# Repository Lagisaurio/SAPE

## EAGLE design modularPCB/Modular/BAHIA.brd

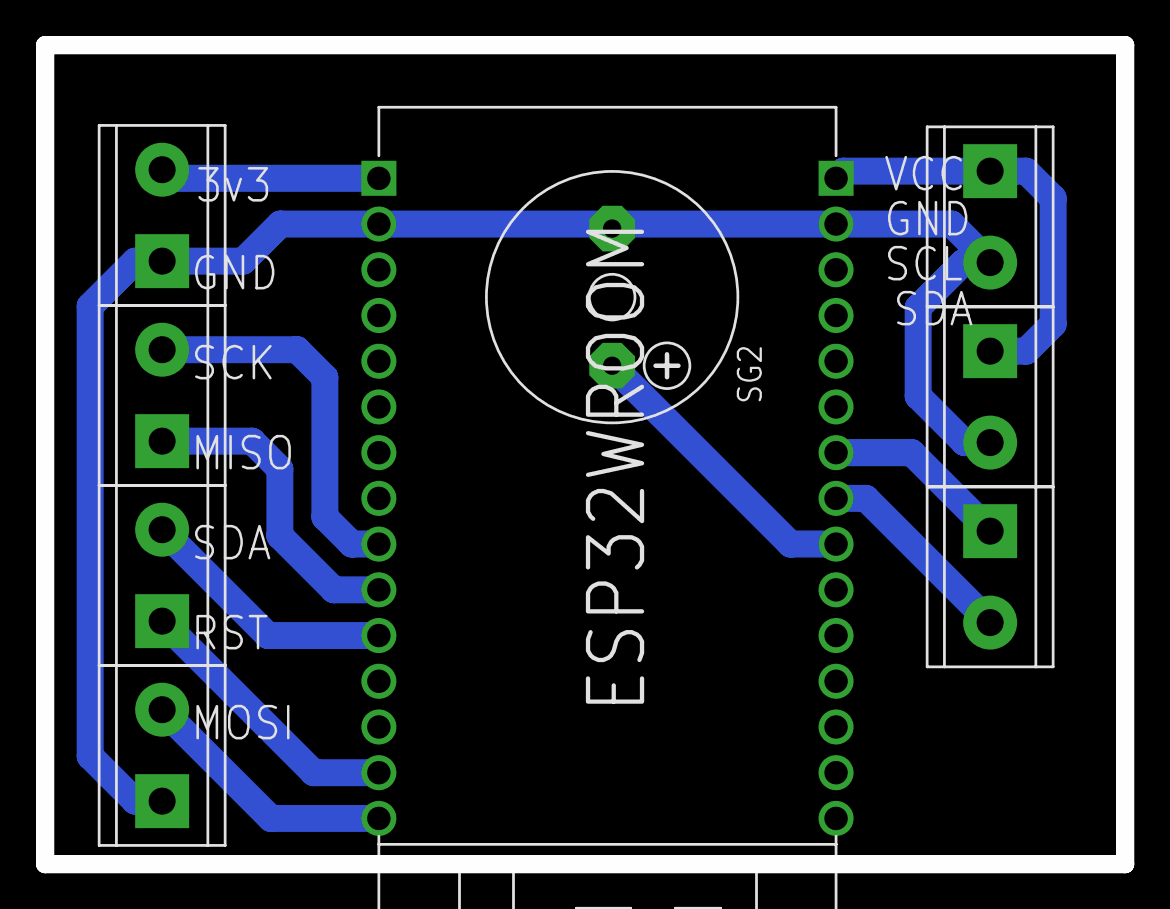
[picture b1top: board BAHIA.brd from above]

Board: 2 copper layers, 60.0 x 45.5 mm, 9 parts (0 on the bottom side), 11 nets.

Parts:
SG2: F/CM12P
U$1: ESP32WROOM
U$2, U$3, U$4, U$5, U$6, U$7, U$8: CLEMAS

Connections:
3V3: U$1.3V3, U$5.2
BUZZER: SG2.+, U$1.D33
GND: SG2.-, U$1.GND@0, U$1.GND@1, U$2.1, U$5.1, U$6.2, U$7.2
MISO: U$1.D19, U$4.1
MOSI: U$1.D23, U$2.2
RST: U$1.D22, U$3.1
SCK: U$1.D18, U$4.2
SCL: U$1.D26, U$8.1
SDA: U$1.D21, U$3.2
SDA_I2C: U$1.D25, U$8.2
VCC: U$1.VIN, U$6.1, U$7.1

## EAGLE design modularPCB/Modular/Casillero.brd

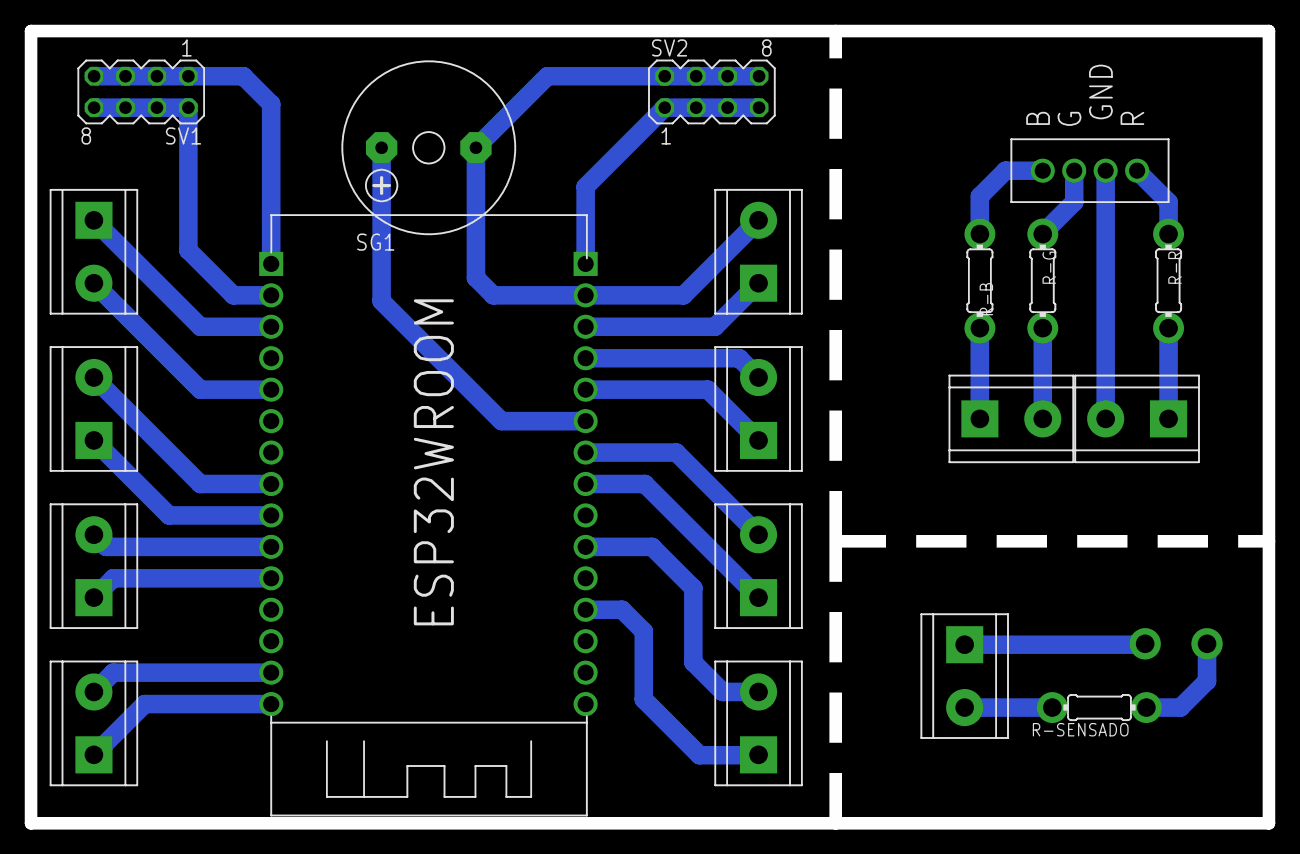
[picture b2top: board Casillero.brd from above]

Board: 2 copper layers, 100.0 x 64.0 mm, 20 parts (0 on the bottom side), 22 nets.

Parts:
R-B: 220; 0204/7
R-G: 220; 0204/7
R-R: 220; 0204/7
R-SENSADO: 220; 0204/7
SG1: F/CM12P
SV1, SV2: MA04-2
U$1: ESP32WROOM
U$2, U$4, U$5, U$6, U$7, U$8, U$9, U$10, U$11, U$12, U$13: CLEMAS
U$3: LEDRGB

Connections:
3V3: SV1.1, SV1.3, SV1.5, SV1.7, U$1.3V3
BUZZER: SG1.+, U$1.D27
CERRADURA_CTRL: U$1.D25, U$8.1
CERRADURA_VCC: U$1.D26, U$8.2
GA_DT: U$1.D19, U$4.2
GA_LED: U$1.D21, U$4.1
GA_SCK: U$1.D18, U$5.1
GND: SG1.-, SV1.2, SV1.4, SV1.6, SV1.8, SV2.2, SV2.4, SV2.6, SV2.8, U$1.GND@0, U$1.GND@1, U$3.GND, U$10.2, U$12.2, U$13.1
IR: U$1.D34, U$7.1
LCD_SCL: U$1.D5, U$5.2
LCD_SDA: U$1.D15, U$6.1
LED_B: R-B.2, U$1.D14, U$9.1, U$11.1
LED_G: R-G.2, U$1.D12, U$9.2, U$11.2
LED_R: R-R.2, U$1.D13, U$10.1, U$12.1
unnamed: R-R.1, U$3.R
unnamed: R-G.1, U$3.G
unnamed: R-B.1, U$3.B
SENSADO_LED: R-SENSADO.2, U$1.D4, U$6.2, U$13.2
UL_ECHO: U$1.D22, U$2.2
UL_LED: U$1.D32, U$7.2
UL_TRG: U$1.D23, U$2.1
VIN: SV2.1, SV2.3, SV2.5, SV2.7, U$1.VIN

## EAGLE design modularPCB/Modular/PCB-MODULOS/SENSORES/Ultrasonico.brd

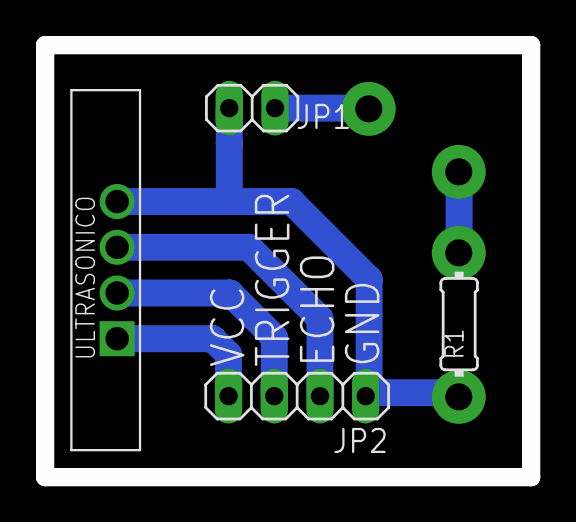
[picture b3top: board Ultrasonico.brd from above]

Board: 2 copper layers, 27.0 x 24.0 mm, 4 parts (0 on the bottom side), 5 nets.

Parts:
JP1: 1X02
JP2: 1X04
R1: 220; 0204/7
U$1: ULTRASONICO

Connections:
ECHO: JP2.2, U$1.ECHO
GND: JP1.2, JP2.1, R1.1, U$1.GND
PULSO-ULTRASONICO: JP1.1, R1.2
TRIGGER: JP2.3, U$1.TRIG
VCC: JP2.4, U$1.VCC

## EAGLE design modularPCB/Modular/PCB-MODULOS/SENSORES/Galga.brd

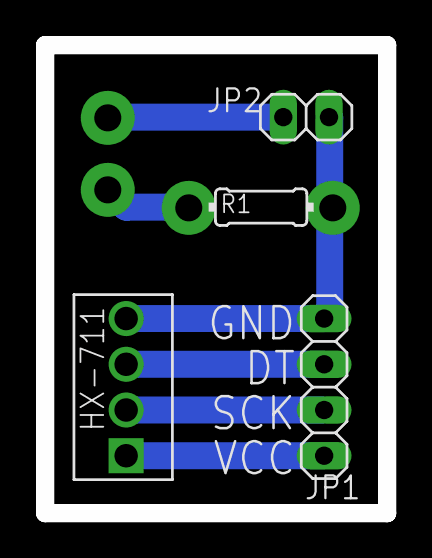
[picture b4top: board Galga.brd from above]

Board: 2 copper layers, 19.0 x 26.0 mm, 4 parts (0 on the bottom side), 4 nets.

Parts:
JP1: 1X04
JP2: 1X02
R1: 220; 0204/7
U$2: HX-711

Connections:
3V3: JP1.4, U$2.VCC
DT-GALGA: JP1.2, U$2.DT
GND: JP1.1, JP2.2, R1.1, U$2.GND
SCK-GALGA: JP1.3, U$2.SCK

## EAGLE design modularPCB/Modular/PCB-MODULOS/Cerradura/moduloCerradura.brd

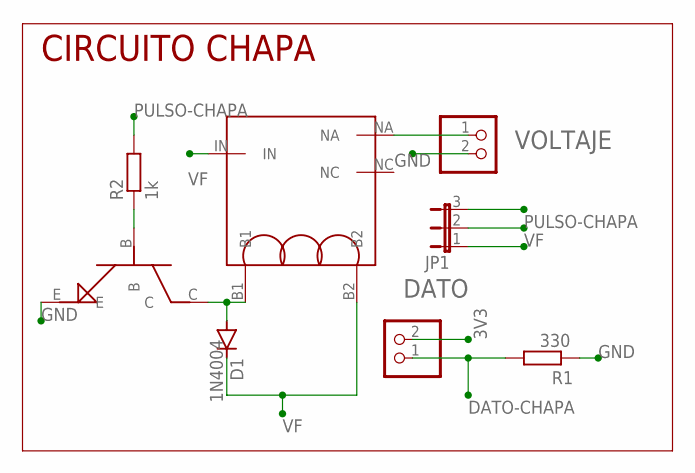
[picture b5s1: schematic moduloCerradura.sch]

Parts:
D1: 1N4004; DO41-10
DATO: PINHD-1X2; 1X02
JP1: JP2E; JP2
R1: 330; 0204/7
R2: 1k; 0204/7
U$1: 2N2222
U$2: RELEY
VOLTAJE: PINHD-1X2; 1X02

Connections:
3V3: DATO.2
DATO-CHAPA: DATO.1, R1.2
GND: JP1.3, R1.1, U$1.E, VOLTAJE.2
unnamed: R2.1, U$1.B
unnamed: D1.A, U$1.C, U$2.B1
unnamed: U$2.NA, VOLTAJE.1
PULSO-CHAPA: JP1.2, R2.2
VF: D1.C, JP1.1, U$2.B2, U$2.IN

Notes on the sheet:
CIRCUITO CHAPA

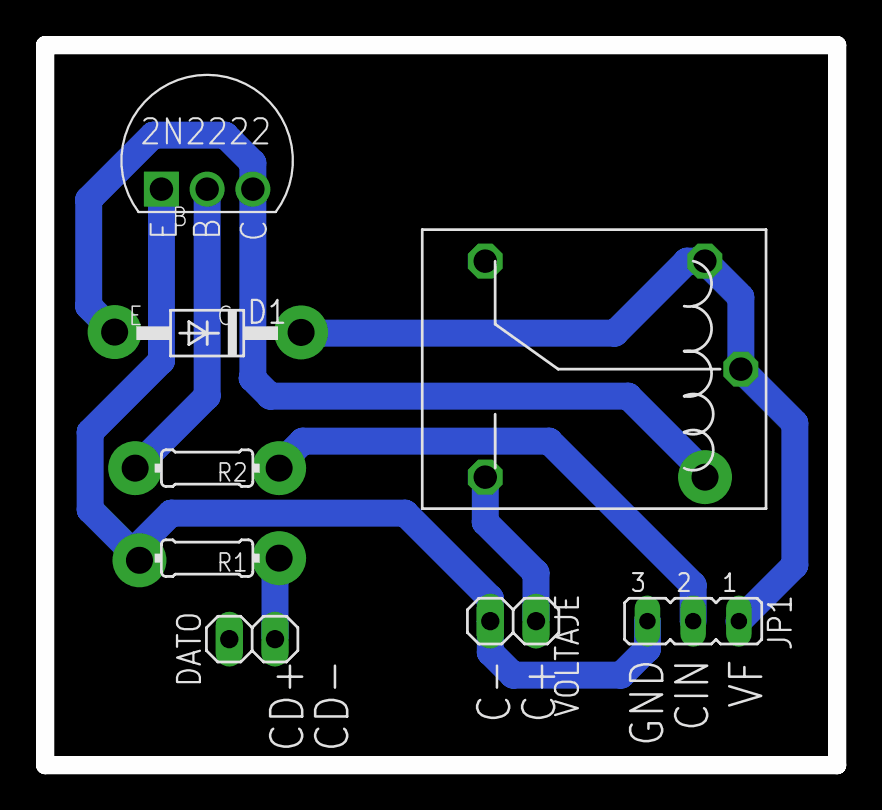
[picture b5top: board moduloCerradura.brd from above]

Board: 2 copper layers, 44.0 x 40.0 mm, 8 parts (0 on the bottom side), 7 nets.

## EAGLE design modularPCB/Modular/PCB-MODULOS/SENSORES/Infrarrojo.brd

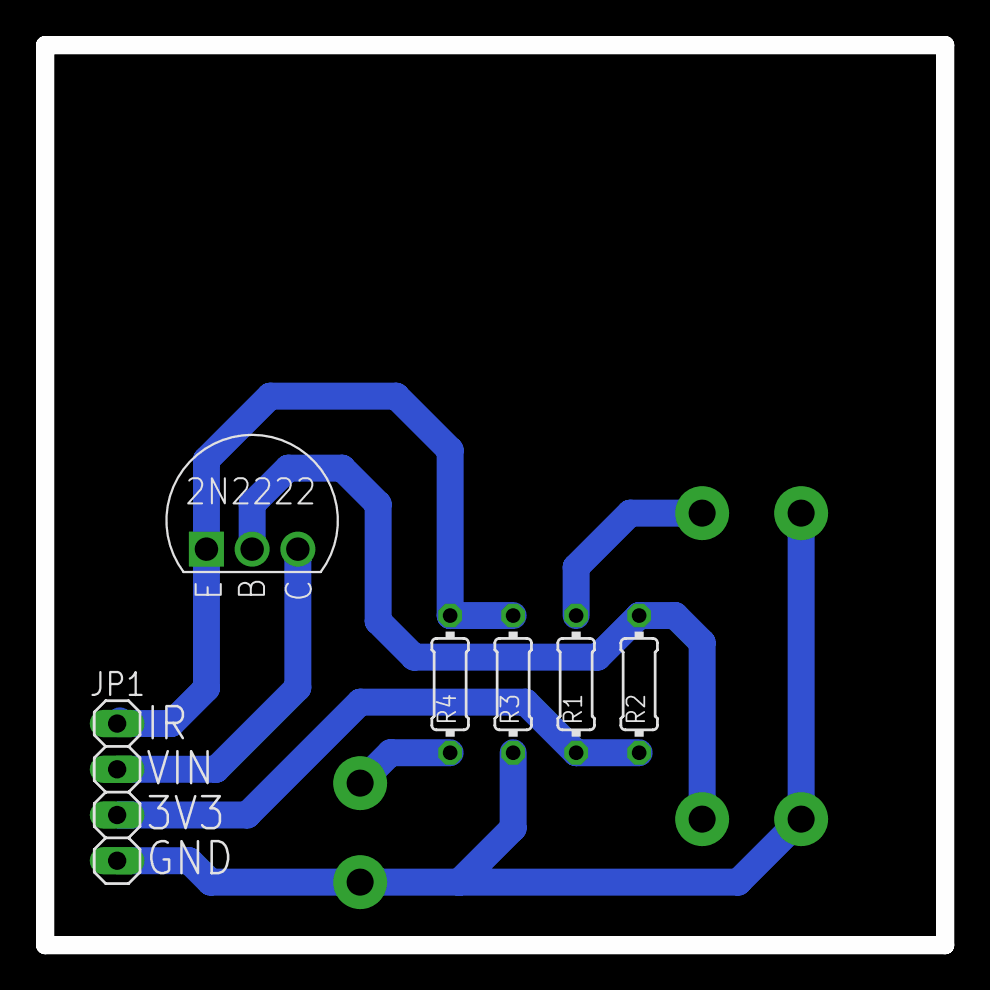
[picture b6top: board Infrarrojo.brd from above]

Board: 2 copper layers, 50.0 x 50.0 mm, 6 parts (0 on the bottom side), 5 nets.

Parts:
JP1: 1X04
R1: 380; 0204/7
R2, R3: 22K; 0204/7
R4: 220; 0204/7
U$1: 2N2222

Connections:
3V3: JP1.2, R1.2, R2.2
GND: JP1.1, R3.2
PULSO-INFRA: JP1.4, R3.1, R4.2, U$1.E
RECEPTOR: R2.1, U$1.B
VIN: JP1.3, U$1.C

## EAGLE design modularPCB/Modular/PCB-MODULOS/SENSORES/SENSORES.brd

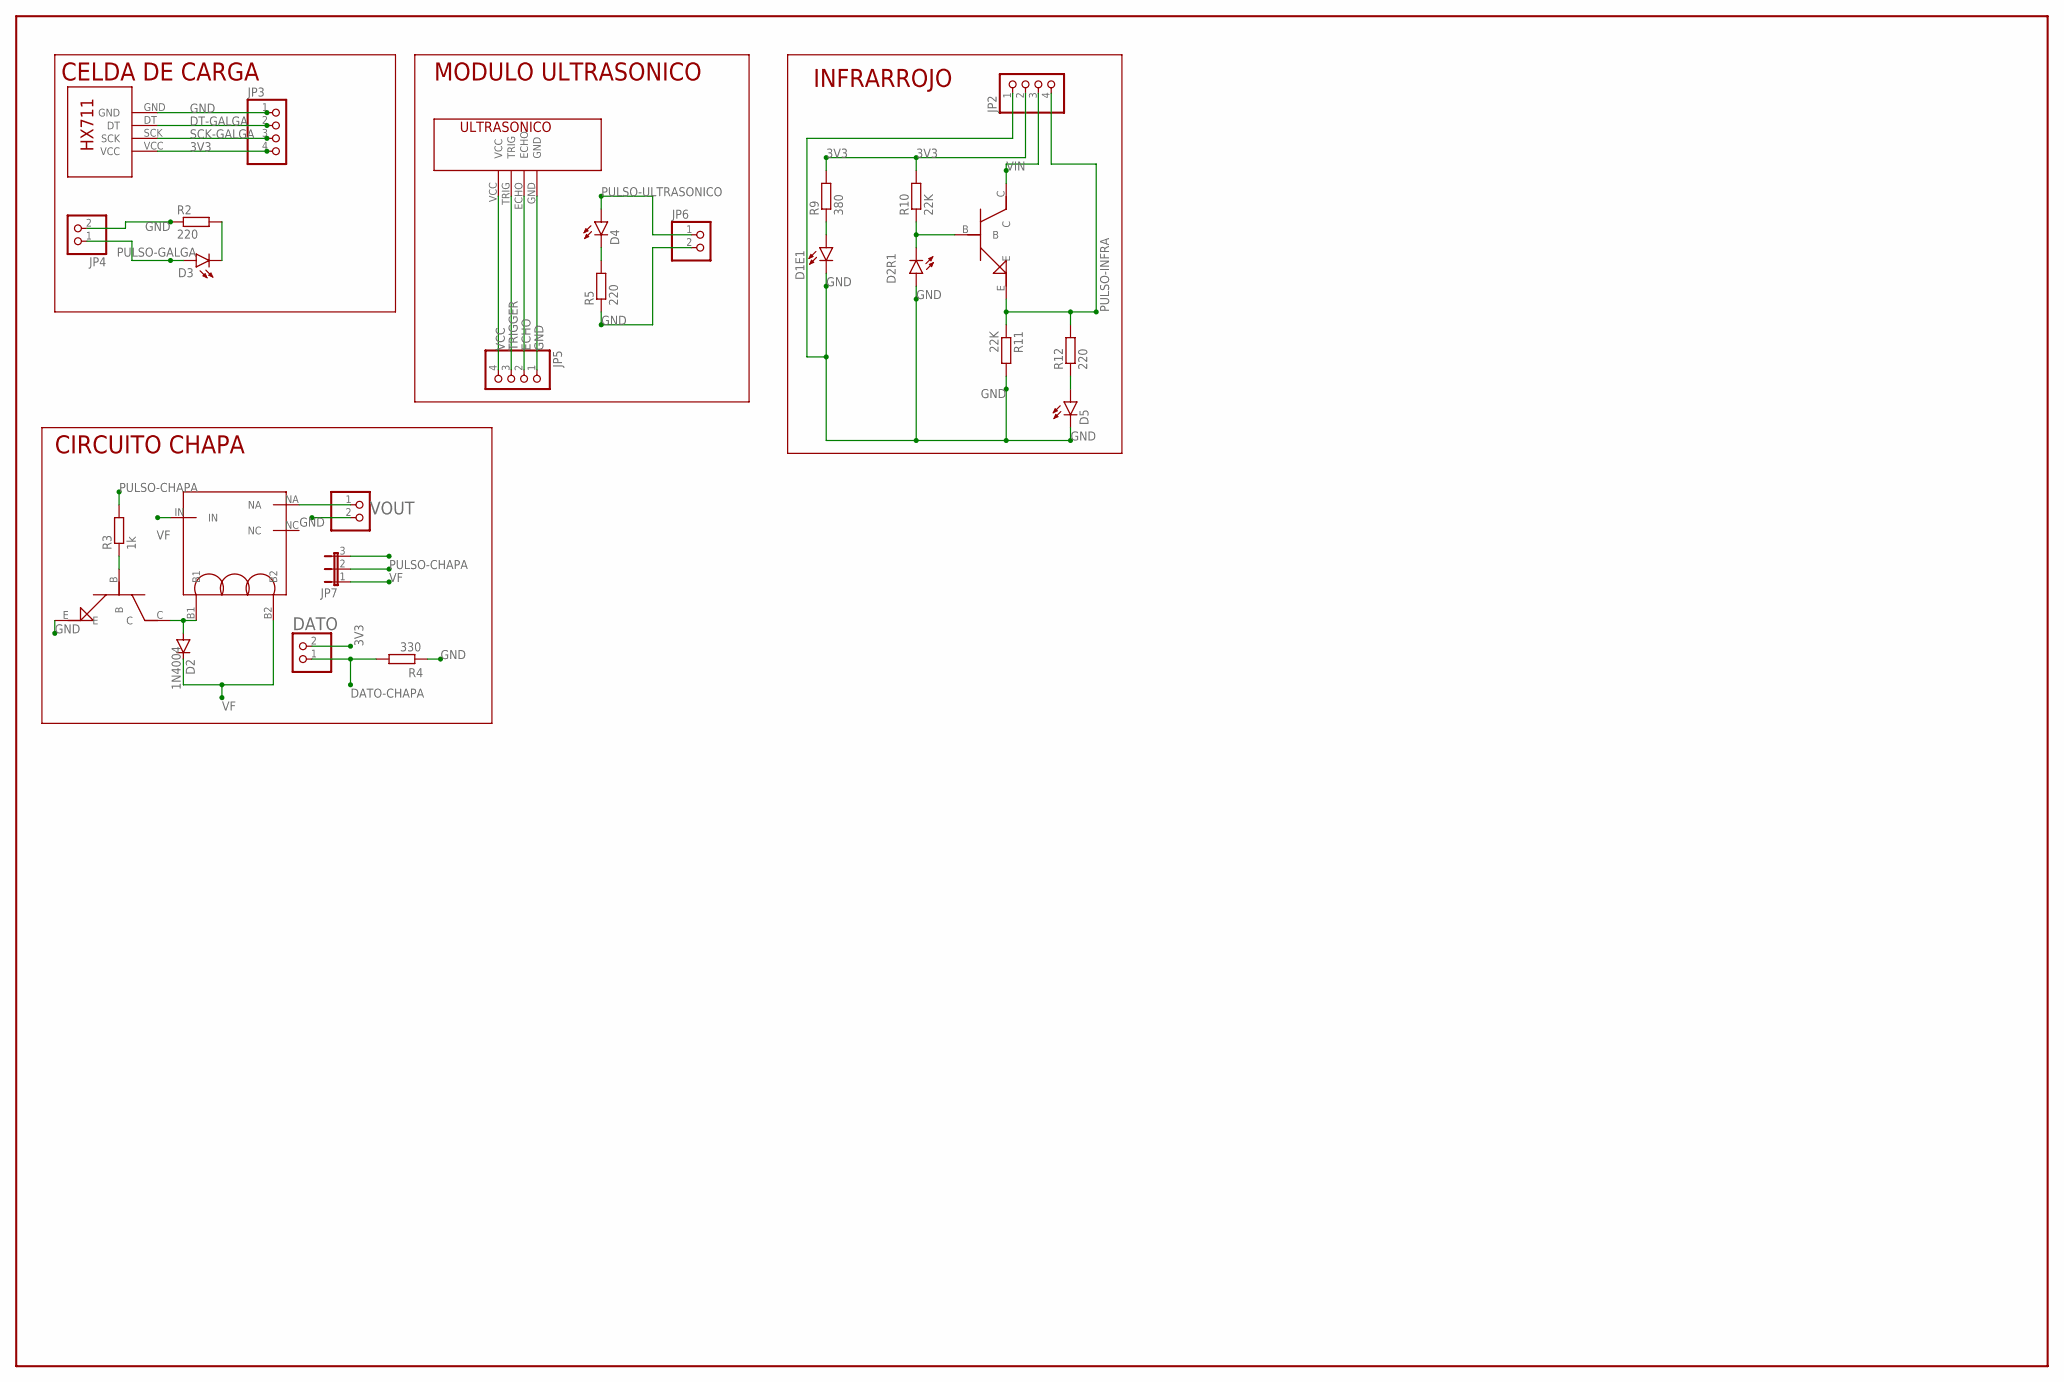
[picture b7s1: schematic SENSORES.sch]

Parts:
D1E1, D2R1, D3, D4, D5: LED3MM
D2: 1N4004; DO41-10
DATO: PINHD-1X2; 1X02
JP2, JP3, JP5: PINHD-1X4; 1X04
JP4, JP6: PINHD-1X2; 1X02
JP7: JP2E; JP2
R2, R5, R12: 220; 0204/7
R3: 1k; 0204/7
R4: 330; 0204/7
R9: 380; 0204/7
R10, R11: 22K; 0204/7
U$1: HX-711
U$2, U$5: 2N2222
U$3: ULTRASONICO
U$7: RELEY
VOUT: PINHD-1X2; 1X02

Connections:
3V3: DATO.2, JP2.2, JP3.4, R9.2, R10.2, U$1.VCC
DATO-CHAPA: DATO.1, R4.2
DT-GALGA: JP3.2, U$1.DT
ECHO: JP5.2, U$3.ECHO
GND: D1E1.K (C), D2R1.A, D5.K (C), JP2.1, JP3.1, JP4.2, JP5.1, JP6.2, JP7.3, R2.1, R4.1, R5.1, R11.2, U$1.GND, U$3.GND, U$5.E, VOUT.2
unnamed: D3.K (C), R2.2
unnamed: D1E1.A, R9.1
unnamed: D4.K (C), R5.2
unnamed: D2R1.K (C), R10.1, U$2.B
unnamed: D5.A, R12.1
unnamed: R3.1, U$5.B
unnamed: D2.A, U$5.C, U$7.B1
unnamed: U$7.NA, VOUT.1
PULSO-CHAPA: JP7.2, R3.2
PULSO-GALGA: D3.A, JP4.1
PULSO-INFRA: JP2.4, R11.1, R12.2, U$2.E
PULSO-ULTRASONICO: D4.A, JP6.1
SCK-GALGA: JP3.3, U$1.SCK
TRIGGER: JP5.3, U$3.TRIG
VCC: JP5.4, U$3.VCC
VF: D2.C, JP7.1, U$7.B2, U$7.IN
VIN: JP2.3, U$2.C

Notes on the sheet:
CIRCUITO CHAPA
CELDA DE CARGA
MODULO ULTRASONICO
INFRARROJO

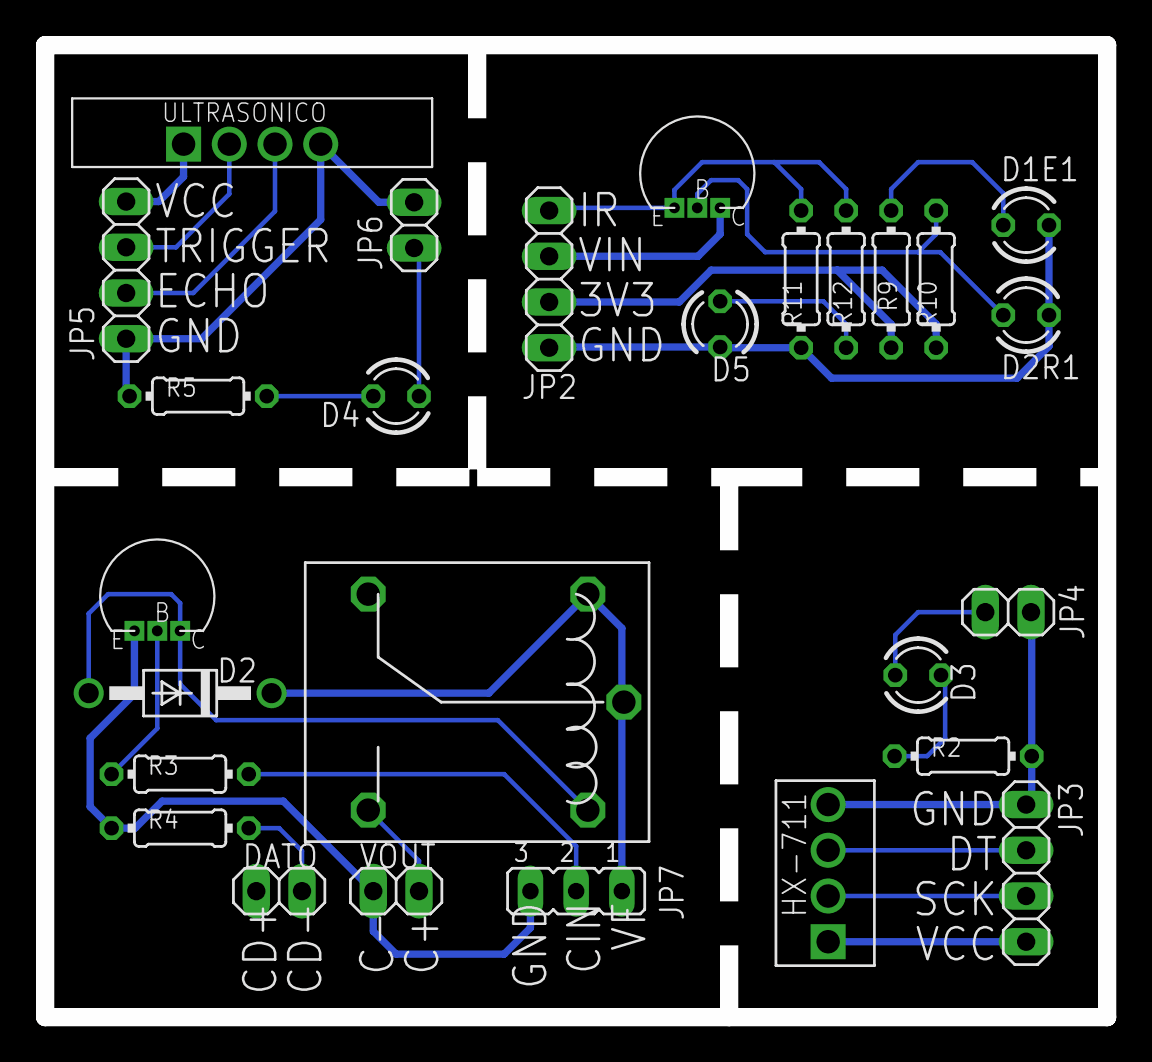
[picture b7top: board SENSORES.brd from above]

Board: 2 copper layers, 59.0 x 54.0 mm, 27 parts (0 on the bottom side), 22 nets.

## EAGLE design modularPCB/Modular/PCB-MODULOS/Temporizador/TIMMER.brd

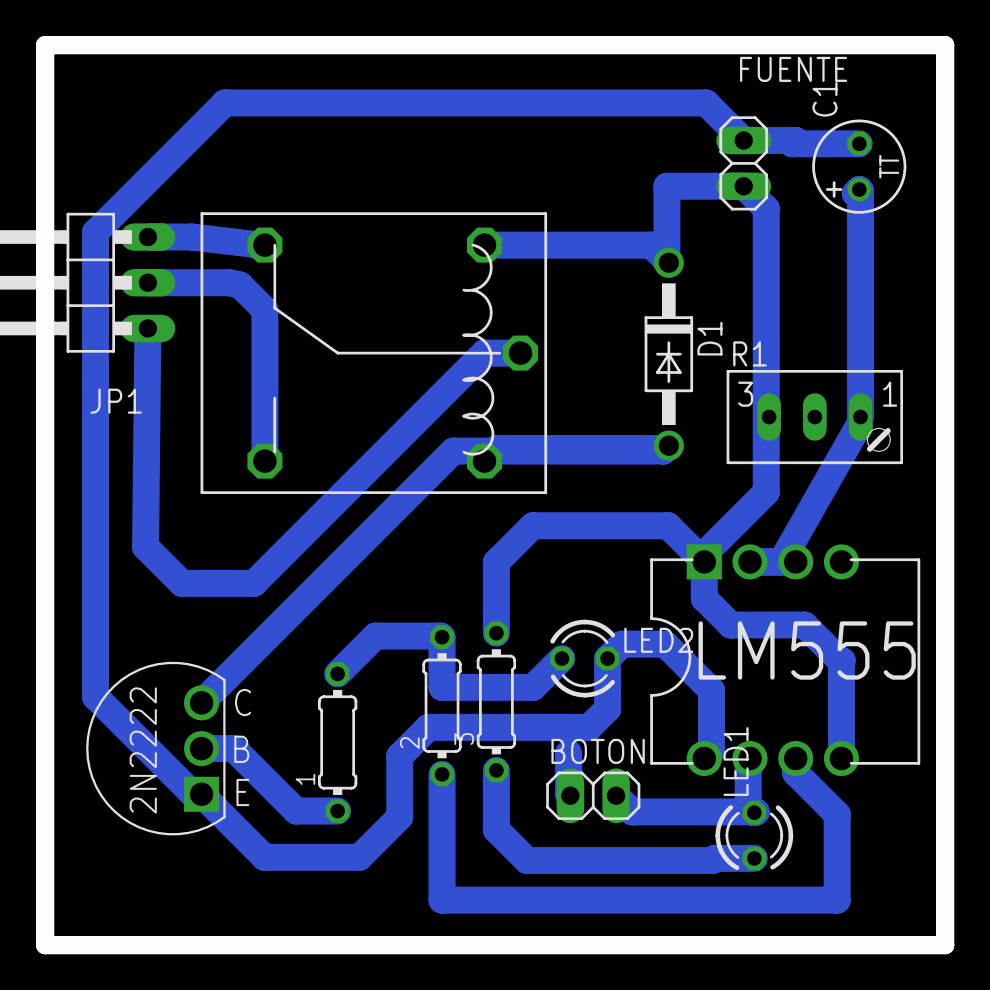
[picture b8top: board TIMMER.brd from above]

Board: 2 copper layers, 50.0 x 50.0 mm, 14 parts (0 on the bottom side), 12 nets.

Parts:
1, 2, 3: 1k; 0204/7
BOTON: 1X02
C1: TT2D5
D1: 1N4004; DO41-10
FUENTE: 1X02
JP1: 1X03/90
LED1, LED2: LED3MM
R1: S64W
U$1: 2N2222
U$2: 555
U$3: RELEY

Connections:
GND: BOTON.1, C1.-, FUENTE.2, LED2.K, U$1.E, U$2.GND
unnamed: D1.A, U$1.C, U$3.B1
unnamed: JP1.1, U$3.IN
unnamed: JP1.2, U$3.NA
unnamed: 1.1, U$1.B
unnamed: 1.2, 2.2, LED2.A
unnamed: 2.1, U$2.OUTPUT
unnamed: BOTON.2, LED1.K, U$2.TRIGGER
unnamed: 3.1, LED1.A
unnamed: JP1.3, U$3.NC
unnamed: C1.+, R1.A, U$2.DISCHARGE, U$2.THRESHOLD
VCC: 3.2, D1.C, FUENTE.1, U$2.RESET, U$2.VCC, U$3.B2

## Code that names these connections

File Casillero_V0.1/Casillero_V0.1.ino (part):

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#define IR_PIN                34                // Pin del ESP32 conectado a la salida sensor infrarrojo.

  //Ultrasonico
#define TRIGGER_PIN           23                // Pin del ESP32 conectado al pin TRIGGER del sensor ultrasónico.
#define ECHO_PIN              22                // Pin del ESP32 conectado al pin ECHO sensor ultrasónico.
#define LED_ULTRASONICO       32                // Pin del ESP32 conectado a un LED para verificar el funcionamiento del sensor ultrasonico .
#define DISTANCIA_MINIMA      7                 // Distancia mínima configurada a la que el sensor ultrasonico verifica la existencia de un objeto (en centímetros).
  
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#define LED_GALGA             21                // Pin del ESP32 conectado a un LED para verificar el funcionamiento de la celda d carga.

  //Indicadores visuales
#define LED_G                 12                // Pin del LED que indica que el casillero está disponible
#define LED_R                 13                // Pin del LED que indica que el casillero está ocupado
#define LED_B                 14                // Pin del LED que funje como alarma
#define LED_SENSADO           4                 // Pin del LED que indica la existencia de un objeto dentro del casillero
#define LED_CONEXION          2                 // Pin del buzzer que funje como alarma

  //Indicadores 
#define BUZZER                27                // Pin del buzzer que emitirá sonido cuando la puerta se encuentre abierta
  
  //Control de cerradura
#define CERRADURA_VCC         26                // Pin que alimenta el modulo analógico para abrir la cerradura
#define CERRADURA_CTRL        35                // Pin que indica el estado de la cerradura.

  //Control LCD
#define SDA_LCD               15                // Pin de SDA para el funcionamiento de la LCD
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void ultrasonico() {

  // Lectura de ultrasonico
  long distancia = medir_distancia(TRIGGER_PIN, ECHO_PIN);
  Serial.println("-----------------------------------------------------");
  Serial.print("Distancia: ");
  Serial.print(distancia);
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}

// 11. Función de control del buzzer
void buzzer(int pinBuzzer, int conteo) {
  for (int i = 0; i < conteo; i++) {
    digitalWrite(pinBuzzer, HIGH);
    delay(500);
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
  //Entradas
  pinMode(IR_PIN, INPUT);
  pinMode(ECHO_PIN, INPUT);
  pinMode(CERRADURA_CTRL, INPUT);

  //Salidas
  pinMode(TRIGGER_PIN, OUTPUT);
  pinMode(LED_R, OUTPUT);
  pinMode(LED_G, OUTPUT);
  pinMode(LED_B, OUTPUT);
  pinMode(LED_SENSADO, OUTPUT);
  pinMode(LED_CONEXION, OUTPUT);
  pinMode(LED_GALGA, OUTPUT);
  pinMode(LED_ULTRASONICO, OUTPUT);
  pinMode(BUZZER, OUTPUT);
  pinMode(CERRADURA_VCC, OUTPUT);

  // Valores iniciales
  digitalWrite(LED_G, HIGH);
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  digitalWrite(CERRADURA_VCC, LOW);

  // Inicializa el sensor ultrasónico
  digitalWrite(TRIGGER_PIN, LOW);
  delayMicroseconds(2);

  // Inicializa la celda de carga
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
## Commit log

2024-12-02 Add: Codigo casillero V0.1
2024-12-02 Add: Codigo de Servidor Pricipal
2024-12-09 Pruba de wifi V0.1
2025-01-24 Encendido de led con Boton mediante WiFi
2025-01-28 Vinculacio wifi de dos casilleros(LED)
2025-01-30 Bahia Modular V1.0 - RFID funcionando correctamente
2025-01-30 Añadio código de sensores ultrasonico y simulación de galga
2025-02-06 Celda de carga funcionando
2025-02-06 Correcciones en IR y se agrega codigo de celda de carga
2025-02-10 Casillero V1.0 - Sensores y WiFi
2025-02-11 LCD AGREGADA
2025-02-13 Actualización general - Vinculación de 2 casilleros, sensores funcionando y led cerradura
2025-02-13 Actualización
2025-02-13 Librerias
2025-02-14 Casilleros diferenciados y Librerías
2025-02-16 Actualización de codigos y se agregan librerias
2025-02-21 Deteccion de cierre de casillero y logica con indicadores
2025-02-24 Prueba: Almacenar archivos de EAGLE CAD
2025-02-25 LCD a codigo, reacomodo de pines y archivos PCB
2025-02-26 Se eliminaron archivos de prueba de EAGLE CAD
2025-02-26 Se eliminaron archivos duplicados
2025-03-05 Actualización de codigos + msj en LCD + comando 'DESOCUPAR'
2025-03-05 Logica en caso de cierre de puertas del casillero junto con ocupación del casillero
2025-03-13 Corrección de errores en codigos más limpios
2025-03-13 Prueba de desconexion (Proceso)
2025-03-21 Proyecto de Eagle
2025-03-21 1. Modulos de PCBs: Ultrasonico, Galga, Infrarrojo, Cerradura; 2. Bloques de diseño de cada modulo
2025-03-21 Librería de Eagle
2025-03-27 Se agrega los archivos gerbers del infrarrojo faltante
2025-03-27 Se elimina archivo erroneo de gerber
2025-03-27 Se agregan archivos gerbers del modulo infrarrojo
2025-03-29 Codigos de prueba de galga
2025-03-29 Actualización de pcbs
2025-03-29 Archivos de materiales y precios
2025-04-04 Corrección de errores en pcbs
2025-04-13 Actualización de diseño PCB: Ancho de líneas
2025-04-13 Se agregaron brd de la ultima actualización
2025-04-14 Actualización de brd y grb de casillero
2025-04-23 Actualización de PCB de bahía: Pistas y borneras
2025-04-23 PDFs e imágenes de los modulos
